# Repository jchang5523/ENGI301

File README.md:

This is an etch a sketch PCB made in EAGLE with the corresponding schematics, board files, bill of materials, screenshots, 
gerber files, and implementation files.

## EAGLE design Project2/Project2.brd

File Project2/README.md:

This is an etch a sketch PCB made in EAGLE with the corresponding schematics, board files, bill of materials, screenshots, 
gerber files, and implementation files.

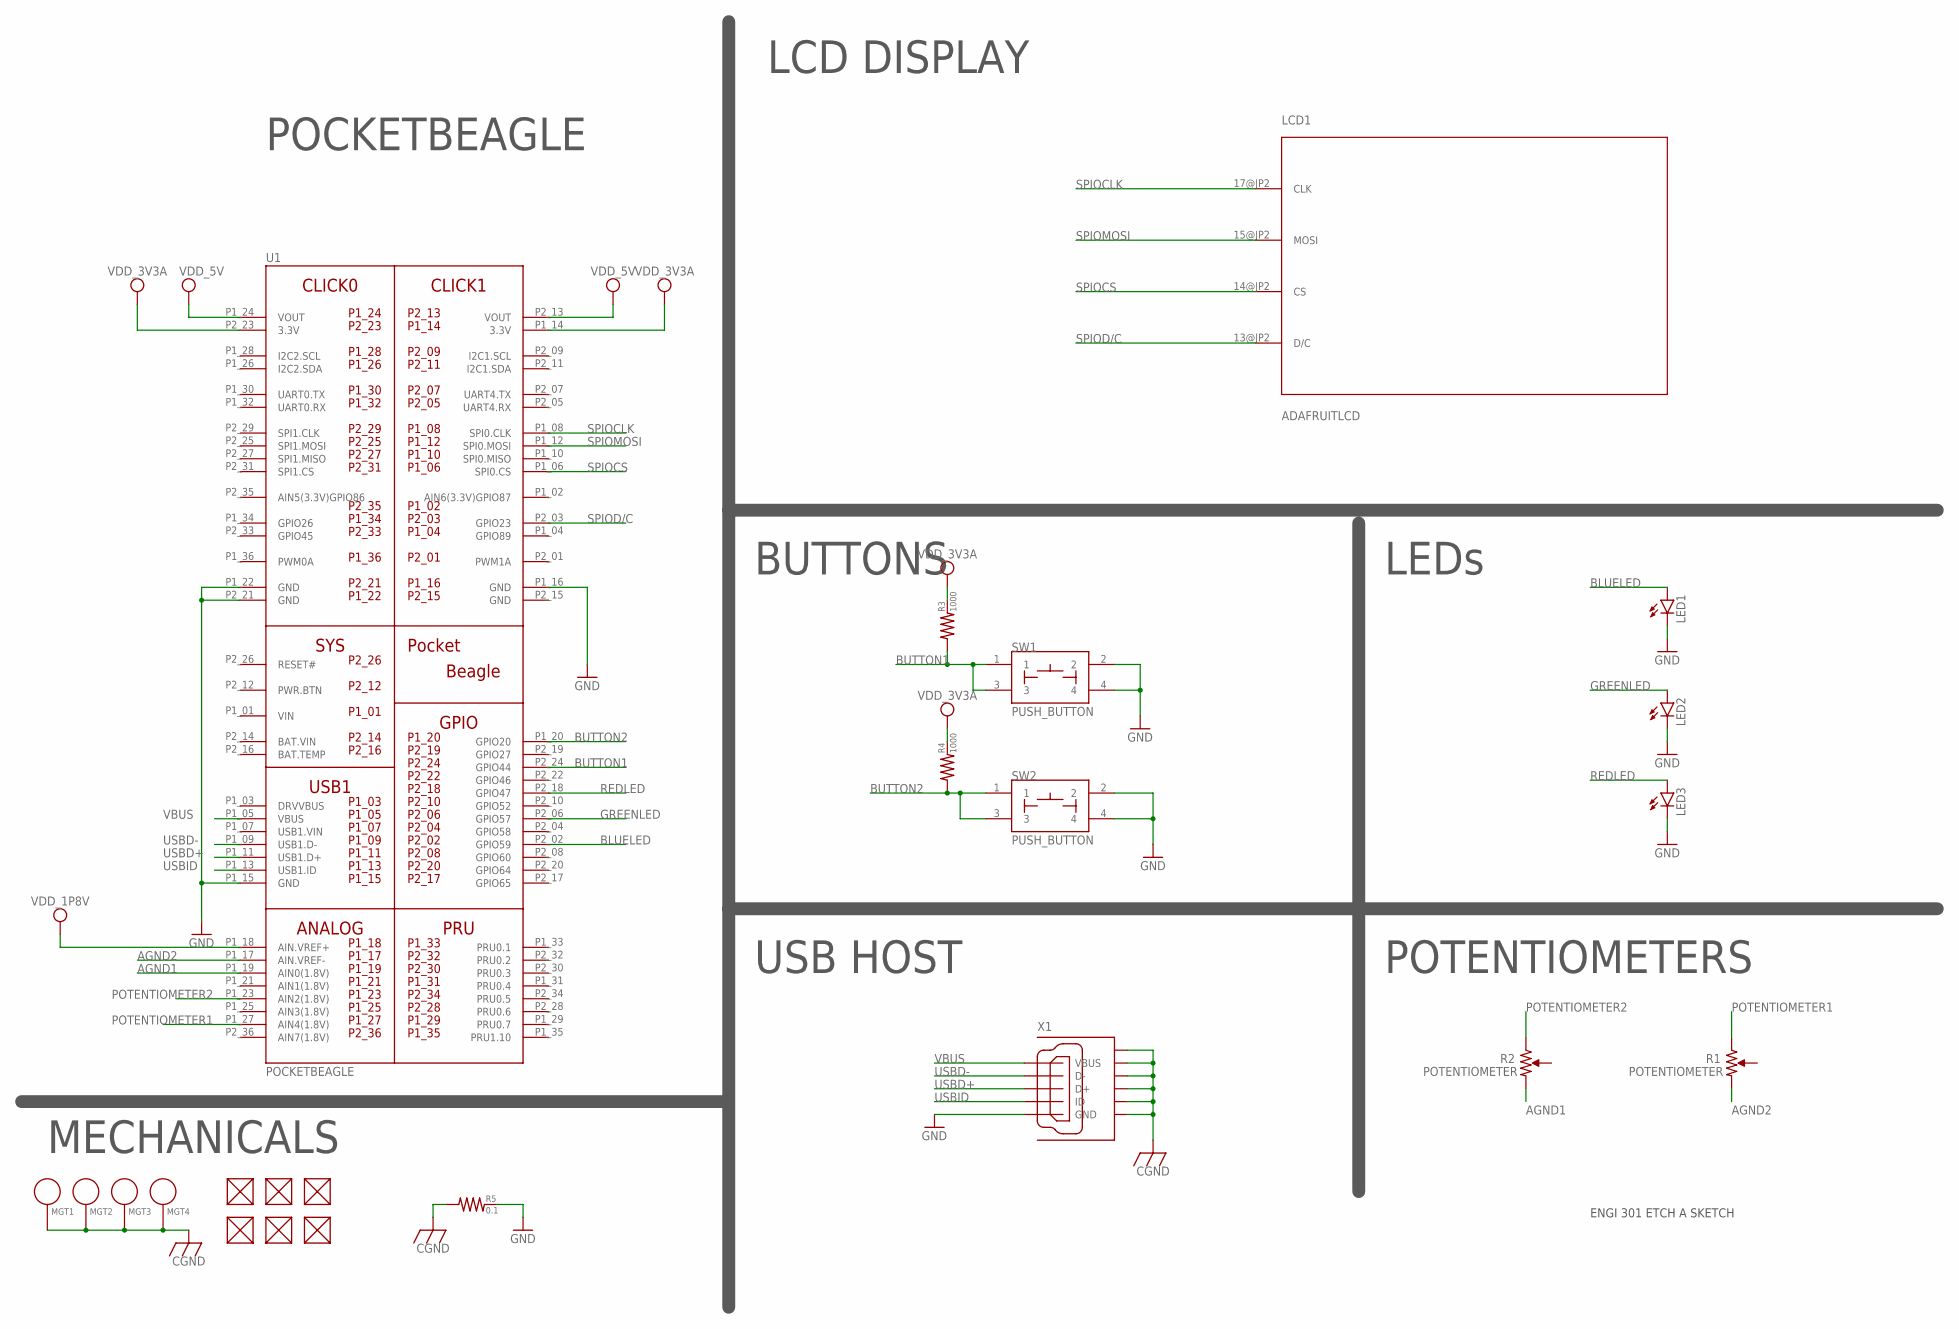
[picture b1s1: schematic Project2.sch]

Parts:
FUD1, FUD2, FUD3, FUD4, FUD5, FUD6: FIDUCIAL; FIDUCIAL_40MIL
LCD1: ADAFRUITLCD; TFTBREAKOUT
LED1, LED2, LED3: LED-(INCH)-0603; 0603-LED
MGT1, MGT2, MGT3, MGT4: MOUNTING_HOLE
R1, R2: POTENTIOMETER; POT-PO90S
R3, R4: 1000; 0402
R5: 0.1; 0805
SW1, SW2: PUSH_BUTTON; BUTTON_12.5MM
U1: POCKETBEAGLE
X1: 10118192-0001LF; 10118192-0001LF(MICRO-USB-B-AMPHENOL-FCI)

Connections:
AGND1: R2.CW, U1.P1_19 (AIN0(1.8V))
AGND2: R1.CW, U1.P1_17 (AIN.VREF-)
BAT.VIN: U1.P2_14 (BAT.VIN)
BLUELED: LED1.A, U1.P2_02 (GPIO59)
BUTTON1: R3.1, SW1.1, SW1.3, U1.P2_24 (GPIO44)
BUTTON2: R4.1, SW2.1, SW2.3, U1.P1_20 (GPIO20)
CGND: MGT1.P$1, MGT2.P$1, MGT3.P$1, MGT4.P$1, R5.1, X1.CGND1 (SGND1), X1.CGND2 (SGND2), X1.CGND3 (SGND3), X1.CGND4 (SGND4), X1.CGND5 (SGND5), X1.CGND6 (SGND6)
GND: LED1.K, LED2.K, LED3.K, R5.2, SW1.2, SW1.4, SW2.2, SW2.4, U1.P1_15 (GND), U1.P1_16 (GND), U1.P1_22 (GND), U1.P2_15 (GND), U1.P2_21 (GND), X1.GND
GREENLED: LED2.A, U1.P2_06 (GPIO57)
POTENTIOMETER1: R1.CCW, U1.P1_27 (AIN4(1.8V))
POTENTIOMETER2: R2.CCW, U1.P1_23 (AIN2(1.8V))
REDLED: LED3.A, U1.P2_18 (GPIO47)
SPIOCLK: LCD1.17@JP2 (CLK), U1.P1_08 (SPI0.CLK)
SPIOCS: LCD1.14@JP2 (CS), U1.P1_06 (SPI0.CS)
SPIOD/C: LCD1.13@JP2 (D/C), U1.P2_03 (GPIO23)
SPIOMOSI: LCD1.15@JP2 (MOSI), U1.P1_12 (SPI0.MOSI)
USBD+: U1.P1_11 (USB1.D+), X1.D+
USBD-: U1.P1_09 (USB1.D-), X1.D-
USBID: U1.P1_13 (USB1.ID), X1.ID
VBUS: U1.P1_05 (VBUS), X1.VBUS
VDD_1P8V: U1.P1_18 (AIN.VREF+)
VDD_3V3A: R3.2, R4.2, U1.P1_14 (3.3V), U1.P2_23 (3.3V)
VDD_5V: U1.P1_24 (VOUT), U1.P2_13 (VOUT)
VIN: U1.P1_01 (VIN)

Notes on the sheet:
LCD DISPLAY
BUTTONS
USB HOST
POTENTIOMETERS
LEDs
POCKETBEAGLE
ENGI 301 ETCH A SKETCH
MECHANICALS

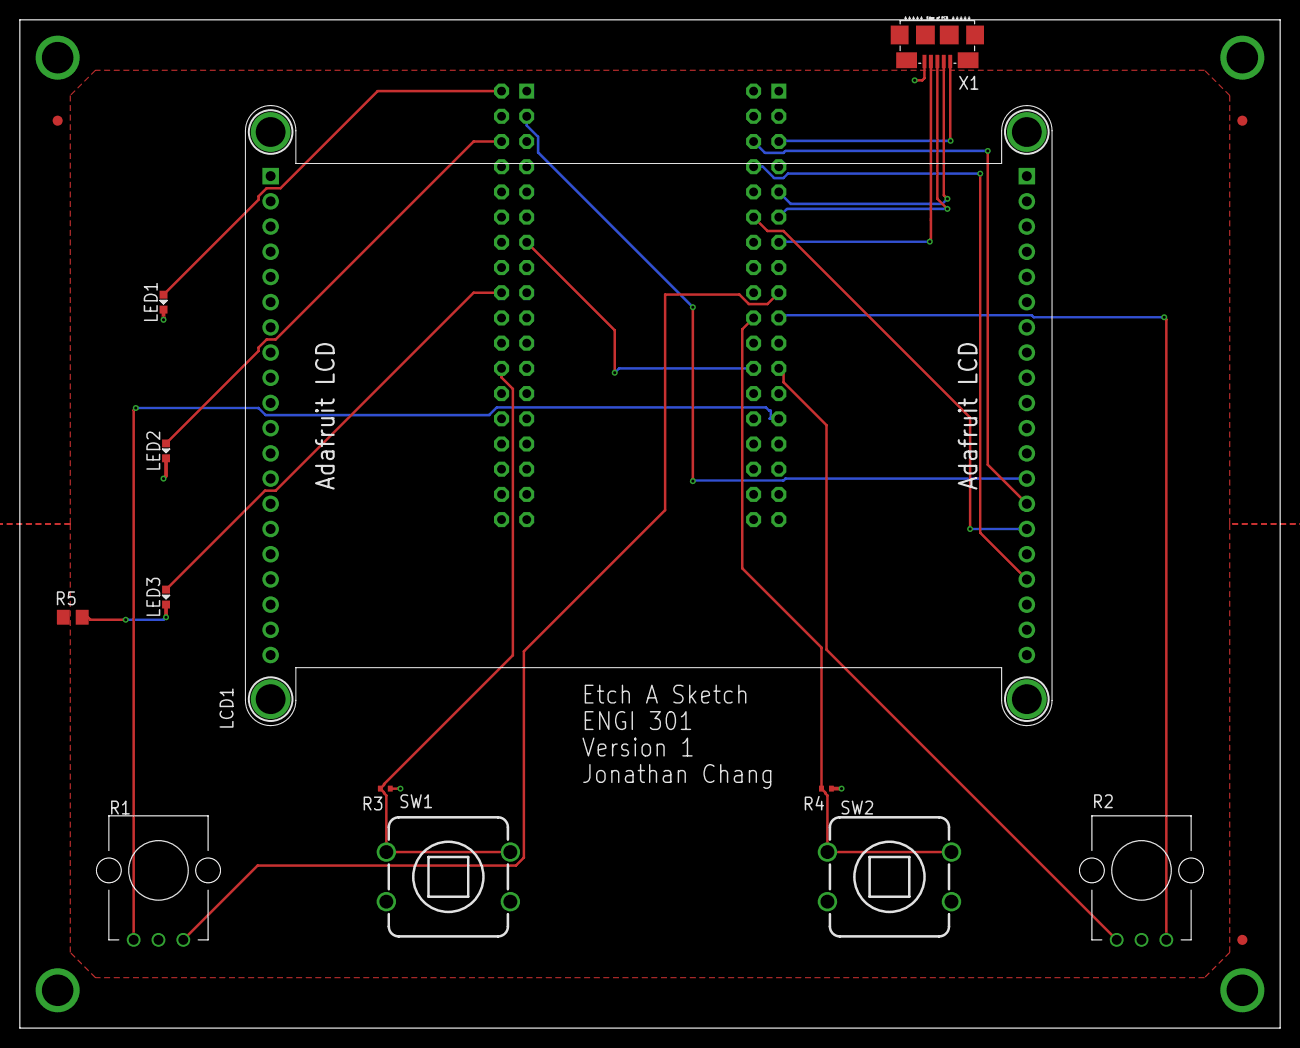
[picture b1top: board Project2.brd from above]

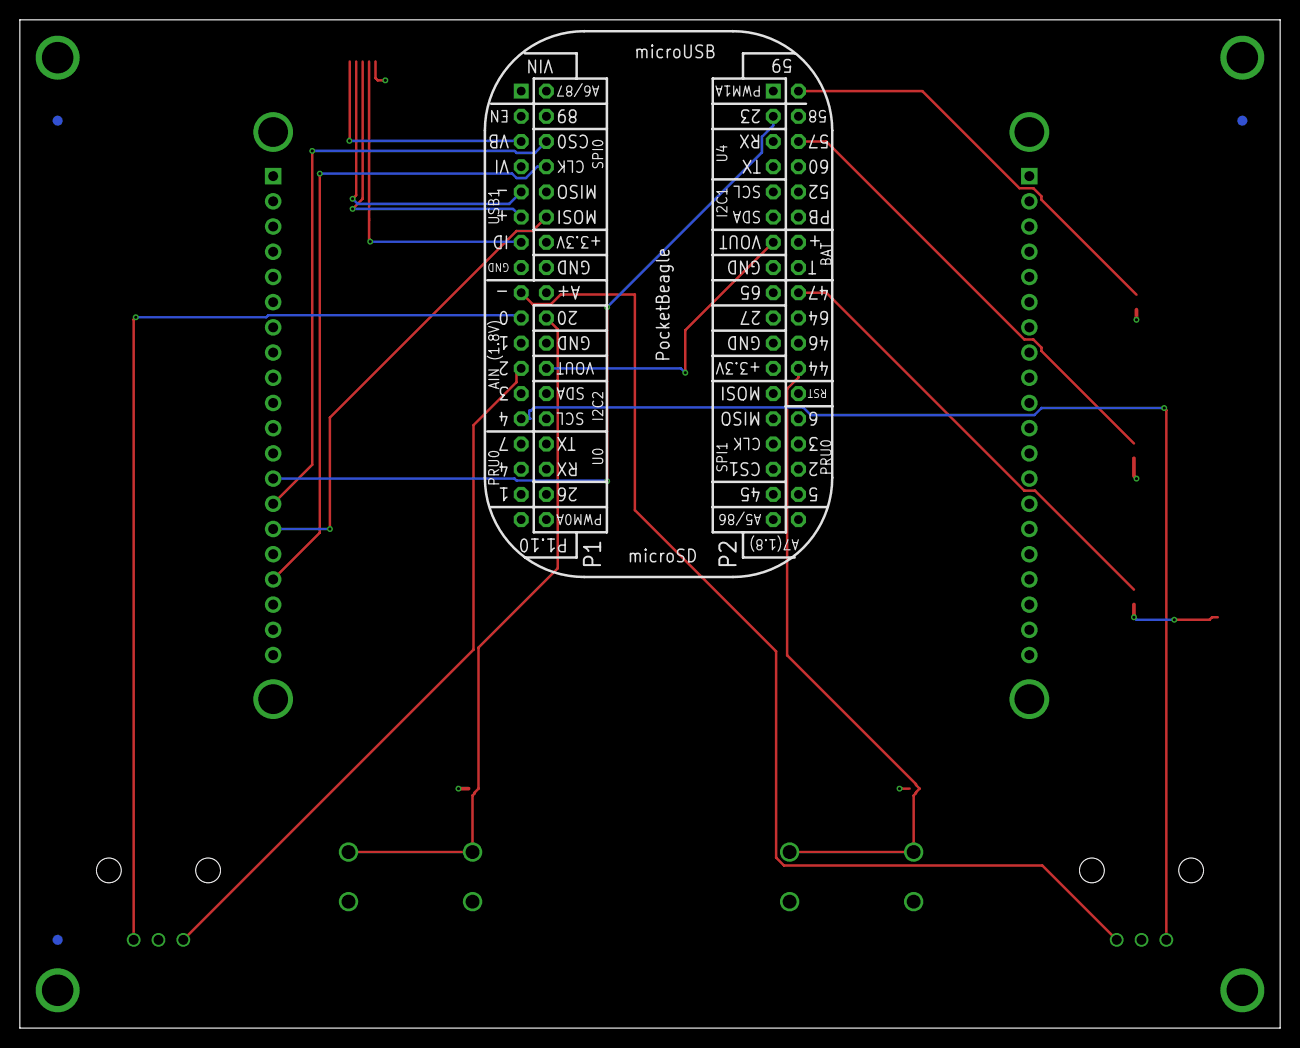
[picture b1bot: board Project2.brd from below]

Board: 4 copper layers, 127.0 x 101.6 mm, 23 parts (4 on the bottom side), 21 nets.

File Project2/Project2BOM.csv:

"Qty";"Value";"Device";"Package";"Parts";"Description";"";
"1";"";"10118192-0001LF";"10118192-0001LF(MICRO-USB-B-AMPHENOL-FCI)";"X1";"Amphenol FCI Micro USB Type B Complete Surface Mount (SMT) no guide holes";"";
"3";"";"LED-(INCH)-0603";"0603-LED";"LED1, LED2, LED3";"Basic SMD LEDs";"";
"1";"0.1";"RESISTOR-(INCH)-0805";"0805";"R5";"Basic SMD Resistors";"";
"2";"1000";"RESISTOR-(INCH)-0402";"0402";"R3, R4";"Basic SMD Resistors";"";
"1";"ADAFRUITLCD";"ADAFRUITLCD";"TFTBREAKOUT";"LCD1";"ILI9341 ADAFRUIT LCD DISPLAY";"";
"6";"FIDUCIAL";"FIDUCIAL";"FIDUCIAL_40MIL";"FUD1, FUD2, FUD3, FUD4, FUD5, FUD6";"";"";
"4";"MOUNTING_HOLE";"MOUNTING_HOLE";"MOUNTING_HOLE";"MGT1, MGT2, MGT3, MGT4";"Chassis Mounting Hole w/GND connection ability";"";
"1";"POCKETBEAGLE";"POCKETBEAGLE";"POCKETBEAGLE";"U1";"";"";
"2";"POTENTIOMETER";"POTENTIOMETER";"POT-PO90S";"R1, R2";"Potentiometer - Examples:";"";
"2";"PUSH_BUTTON";"PUSH_BUTTON";"BUTTON_12.5MM";"SW1, SW2";"";"";

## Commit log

2022-09-26 add calculator
2022-09-26 add blink
2022-09-26 add blink updated
2022-12-04 lights.py
2022-12-04 print
2022-12-04 adding files
2022-12-04 poop
2022-12-05 code update
2022-12-05 code
2022-12-05 12/5 code
2022-12-09 12/9 update
2022-12-11 12/11 update
2022-12-13 Rename README.md to Project2/README.md
